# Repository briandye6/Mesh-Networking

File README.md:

# ENIGMA Mesh Networking Design Project
This repository was designed to be used with the STM32F091RCT ARM Cortex microcontroller.

### Repository Layout:
| File          | Purpose         |
| ------------- |:-------------| 
| src/main.c    | Contains the all interrupt setup functions, interrupt service routines, and GPS, Battery helper functions |
| src/SPI.c     | SPI initialization, write, and read for RFM69HCW Radio and MP2202 TFT Display    |
| src/I2C.c     | I2C initialization, write, and read for Sparkfun Battery Baby Sitter and SAM-M8Q GPS module|
| src/bluetooth.c|  UART initialization, write, and read for HM-19 bluetooth module|
| src/lcd.c|  Helper functions to communicate with MP2202 TFT Display|
| src/RFM69.c|  Helper functions to communicate with RFM69HCW Radio|
| src/STPswitch.c|  Helper functions to create and facilitate a MESH Spanning Tree Protocol|
| src/list.c| Doubly Linked List Data Structure for forwarding table|

### User Interace: Progressive Web Application
https://enigmaterminal.net/

### Final Design Review Presentation Link with VIDEO DEMONSTRATION
https://purdue0-my.sharepoint.com/:p:/g/personal/dye28_purdue_edu/Ee8eXgqAICREm-nx36Vz36ABuLT1QJ_dSffJ5avcmjQzwg?e=PEjIST

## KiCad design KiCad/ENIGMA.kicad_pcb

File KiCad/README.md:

# KiCad files for Printed Circuit Board (PCB) Design

### What is KiCad?
KiCad is a free software that facilitates the design and simulation of electronic hardware.

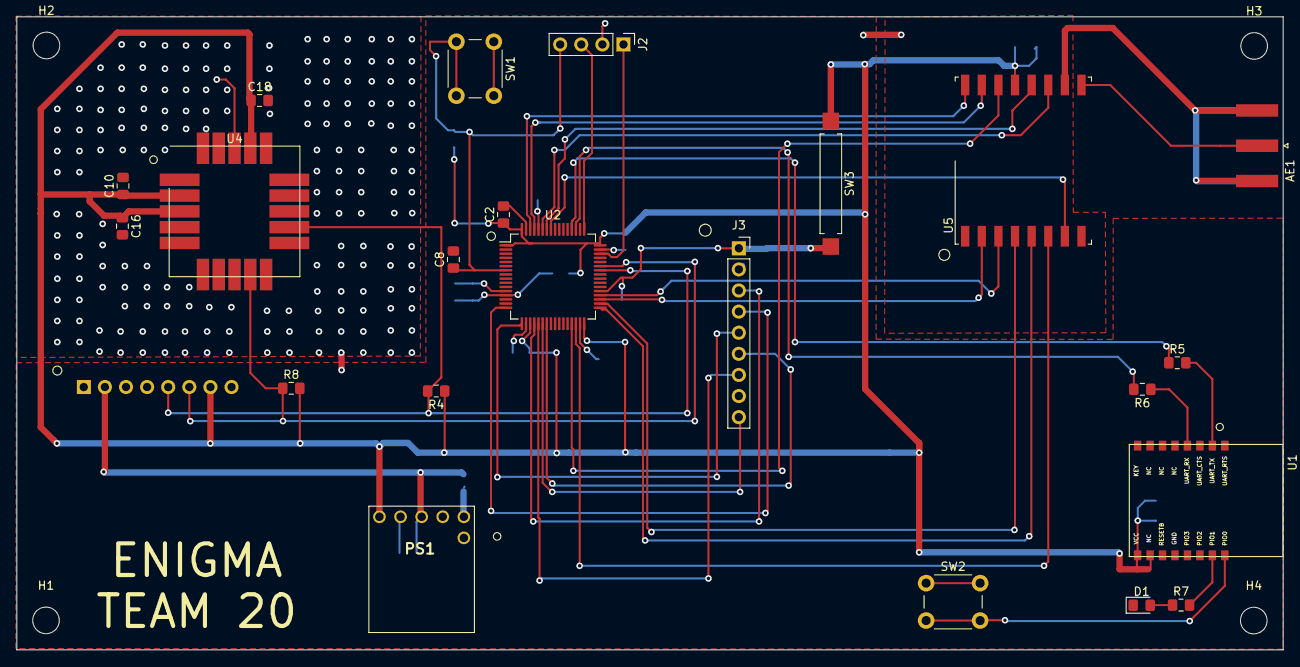
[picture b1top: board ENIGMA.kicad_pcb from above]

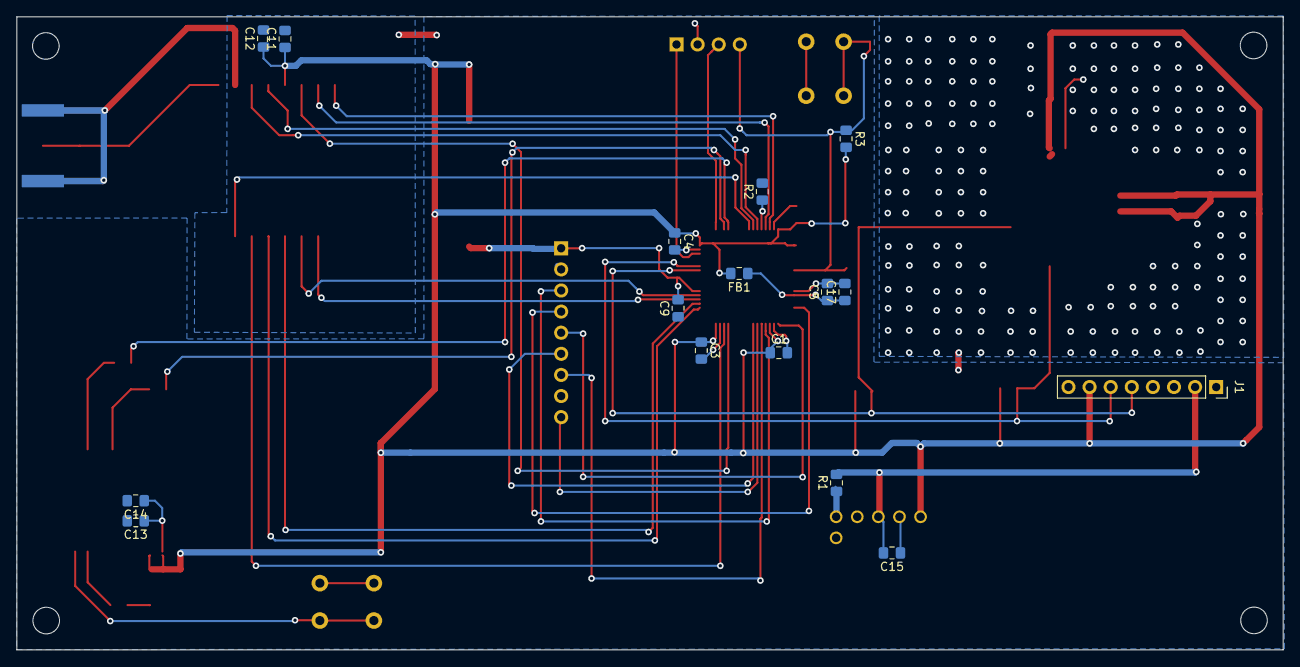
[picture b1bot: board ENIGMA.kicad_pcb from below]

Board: 2 copper layers, 152.4 x 76.2 mm, 42 parts (16 on the bottom side), 37 nets.

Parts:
AE1: Antenna_Shield; SMA_Amphenol_132289_EdgeMount
C1, C2, C3, C4, C5, C8, C9, C10, C11, C13, C17: .1 uF; C_0805_2012Metric_Pad1.15x1.40mm_HandSolder
C12, C15, C16, C18: 4.7 uF; C_0805_2012Metric_Pad1.15x1.40mm_HandSolder
C14: 10 uF; C_0805_2012Metric_Pad1.15x1.40mm_HandSolder
D1: LED; LED_0805_2012Metric_Pad1.15x1.40mm_HandSolder
FB1: 600 Ohm @ 100MHz .3Ohm DCR, 500mA Ferrite Bead; L_0805_2012Metric_Pad1.15x1.40mm_HandSolder
H1, H2, H3, H4: MountingHole; MountingHole_3.2mm_M3
J1: Conn_01x08_Female; PinSocket_1x08_P2.54mm_Vertical
J2: Conn_01x04_Male; PinHeader_1x04_P2.54mm_Vertical
J3: Conn_01x09_Female; PinSocket_1x09_P2.54mm_Vertical
PS1: S9V11F3S5C3
R1, R5, R6: 1K; R_0805_2012Metric_Pad1.15x1.40mm_HandSolder
R2, R3, R4, R8: 100K; R_0805_2012Metric_Pad1.15x1.40mm_HandSolder
R7: 470; R_0805_2012Metric_Pad1.15x1.40mm_HandSolder
SW1, SW2: SW_Push_Dual_x2; SW_PUSH_6mm
SW3: SW_DIP_x01; SW_SPST_REED_CT10-XXXX-G1
U1: HM-19_Bluetooth; hm19_Bluetooth
U2: STM32F091RCTx; LQFP-64_10x10mm_P0.5mm
U4: ublox_SAM-M8Q
U5: RFM69HCW; HOPERF_RFM69HW

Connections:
+3V0: C1.1, C2.1, C3.1, C4.1, C10.1, C11.1, C12.1, C13.1, C14.1, C16.1, C18.1, FB1.2, J1.7, PS1.6, R3.2, R4.1, R8.2, SW3.2, U1.9, U1.10, U2.1, U2.19, U2.32, U2.48, U2.64, U4.2, U4.3, U4.17, U5.13
+5V: C15.2, J1.2, PS1.4, R1.2
/3VA: C5.1, C17.1, FB1.1, U2.13
/NRST: C8.1, J2.4, R3.1, SW1.2, U2.7
/PA2: J3.4, U2.16
/PA3: J3.5, U2.17
/PA4: J3.3, U2.20
/PA5: J3.7, U2.21
/PA6: J3.9, U2.22
/PA7: J3.6, U2.23
/PA9: J1.5, R4.2, U2.42, U4.12
/PA10: J1.6, R8.1, U2.43, U4.9
/PB5: U2.57, U5.7
/PB6: U2.58, U5.12
/PB7: U2.59, U5.11
/PB8: U2.61, U5.15
/PB9: U2.62, U5.16
/PB10: U2.29, U5.14
/PB11: U2.30, U5.6
/PB12: U2.33, U5.5
/PB13: U2.34, U5.4
/PB14: U2.35, U5.2
/PB15: U2.36, U5.3
/PC6: C9.2, J3.1, SW3.1, U2.37
/PC10: R6.2, U2.51
/PC11: R5.1, U2.52
BOOT0: R2.1, U2.60
GND: AE1.2, C1.2, C2.2, C3.2, C4.2, C5.2, C8.2, C9.1, C10.2, C11.2, C12.2, C13.2, C14.2, C15.1, C16.2, C17.2, C18.2, D1.1, J1.1, J2.2, J3.2, PS1.1, PS1.5, R2.2, SW1.1, SW2.1, U1.12, U2.12, U2.18, U2.31, U2.47, U2.63, U4.1, U4.4, U4.5, U4.6, U4.10, U4.11, U4.15, U4.16, U4.20, U5.1, U5.8, U5.10
unnamed: AE1.1, U5.9
unnamed: D1.2, R7.1
unnamed: PS1.2, R1.1
unnamed: R5.2, U1.2
unnamed: R6.1, U1.4
unnamed: R7.2, U1.15
unnamed: SW2.2, U1.16
SWCLK: J2.3, U2.49
SWDIO: J2.1, U2.46

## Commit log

2022-07-06 Basic API README
2022-07-06 KiCad PCB Design
2022-07-06 KiCad Directory
2022-07-06 Rename Analog_DAC.dcm to KiCad/Analog_DAC.dcm
2022-07-06 Rename Analog_DAC.lib to KiCad/Analog_DAC.lib
2022-07-06 Rename Connector_Generic.dcm to KiCad/Connector_Generic.dcm
2022-07-06 Rename Connector_Generic.lib to KiCad/Connector_Generic.lib
2022-07-06 Rename ENIGMA-cache.lib to KiCad/ENIGMA-cache.lib
2022-07-06 Rename ENIGMA-rescue.dcm to KiCad/ENIGMA-rescue.dcm
2022-07-06 Rename ENIGMA-rescue.lib to KiCad/ENIGMA-rescue.lib
2022-07-06 Rename ENIGMA.kicad_pcb to KiCad/ENIGMA.kicad_pcb
2022-07-06 Rename ENIGMA.kicad_pcb-bak to KiCad/ENIGMA.kicad_pcb-bak
2022-07-06 Rename ENIGMA.kicad_prl to KiCad/ENIGMA.kicad_prl
2022-07-06 Rename ENIGMA.kicad_pro to KiCad/ENIGMA.kicad_pro
2022-07-06 Rename ENIGMA.kicad_sch to KiCad/ENIGMA.kicad_sch
2022-07-06 Rename ENIGMA.net to KiCad/ENIGMA.net
2022-07-06 Rename ENIGMA.pro to KiCad/ENIGMA.pro
2022-07-06 Rename ENIGMA.sch to KiCad/ENIGMA.sch
2022-07-06 Rename ENIGMA.sch-bak to KiCad/ENIGMA.sch-bak
2022-07-06 Rename HM-19_Bluetooth.sym to KiCad/HM-19_Bluetooth.sym
2022-07-06 Rename RF_Bluetooth.dcm to KiCad/RF_Bluetooth.dcm
2022-07-06 Rename RF_Bluetooth.lib to KiCad/RF_Bluetooth.lib
2022-07-06 Rename _autosave-ENIGMA.pro to KiCad/_autosave-ENIGMA.pro
2022-07-06 Rename _autosave-ENIGMA.sch to KiCad/_autosave-ENIGMA.sch
2022-07-06 Rename fp-lib-table to KiCad/fp-lib-table
2022-07-06 Rename hm-19_bluetooth.bck to KiCad/hm-19_bluetooth.bck
2022-07-06 Rename hm-19_bluetooth.dcm to KiCad/hm-19_bluetooth.dcm
2022-07-06 Rename hm-19_bluetooth.lib to KiCad/hm-19_bluetooth.lib
2022-07-06 Rename sym-lib-table to KiCad/sym-lib-table
2022-07-06 Progress Reports
2022-07-06 Midterm Design Review
2022-07-06 Documentation Upload
2022-07-09 File Brief Update
2023-05-03 Add Technical Project Presentation
